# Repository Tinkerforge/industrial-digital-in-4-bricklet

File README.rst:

Industrial Digital In 4 Bricklet
================================

This repository contains the firmware source code and the hardware design
files. The documentation generator configs can be found at
https://github.com/Tinkerforge/generators

Repository Content
------------------

software/:
 * examples/: Examples for all supported languages
 * build/: Compiled files
 * src/: Source code of firmware
 * Makefile: Makefile to build project

hardware/:
 * Contains KiCad project files and additionally schematics as PDF

datasheets/:
 * Contains datasheets for sensors and complex ICs that are used

Hardware
--------

The hardware is designed with the open source EDA Suite KiCad
(http://www.kicad.org). Before you are able to open the files,
you have to install the Tinkerforge kicad-libraries
(https://github.com/Tinkerforge/kicad-libraries). You can either clone
them directly in hardware/ or clone them in a separate folder and
symlink them into hardware/
(ln -s kicad_path/kicad-libraries project_path/hardware). After that you
can open the .pro file in hardware/ with KiCad and from there view and
modify the schematics and the PCB layout.

Software
--------

If you want to do your own Brick/Bricklet firmware development we highly
recommend that you use our build environment setup script and read the
tutorial (https://www.tinkerforge.com/en/doc/Tutorials/Tutorial_Build_Environment/Tutorial.html).

To compile the C code we recommend you to install the newest GNU Arm Embedded
Toolchain (https://launchpad.net/gcc-arm-embedded/+download).
You also need to install bricklib (https://github.com/Tinkerforge/bricklib)
and brickletlib (https://github.com/Tinkerforge/brickletlib).

You can either clone it directly in software/src/ or clone it in a
separate folder and symlink it into software/src/
(ln -s bricklib_path/bricklib project_path/software/src/ and
ln -s brickletlib_path/brickletlib project_path/software/src/).
Finally make sure to have CMake installed
(http://www.cmake.org/cmake/resources/software.html).

After that you can build the firmware by invoking make in software/.
The firmware (.bin) can then be found in software/build/ and uploaded
with brickv (click button "Flashing" on start screen).

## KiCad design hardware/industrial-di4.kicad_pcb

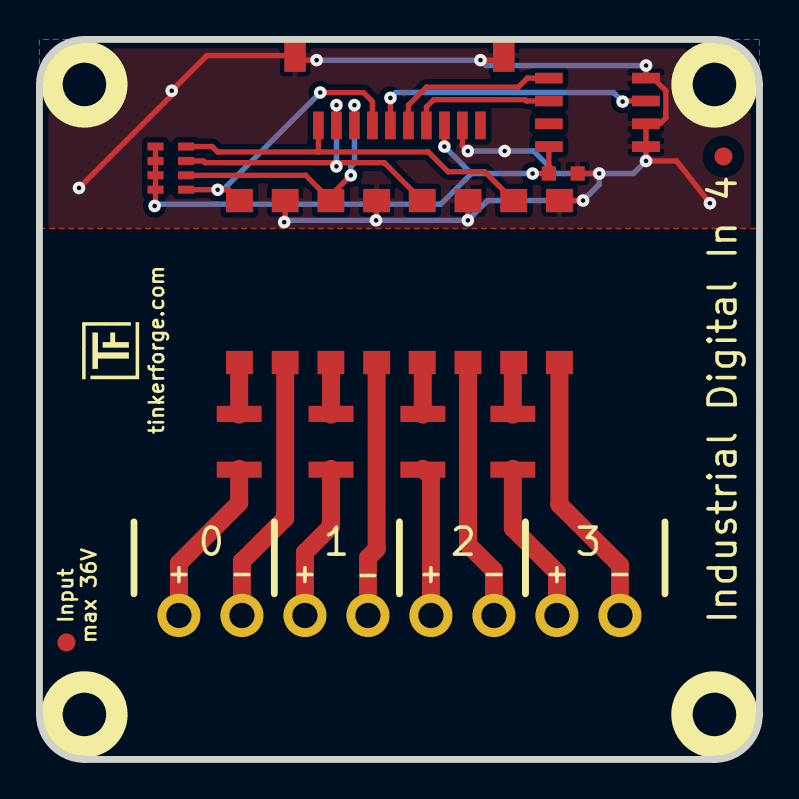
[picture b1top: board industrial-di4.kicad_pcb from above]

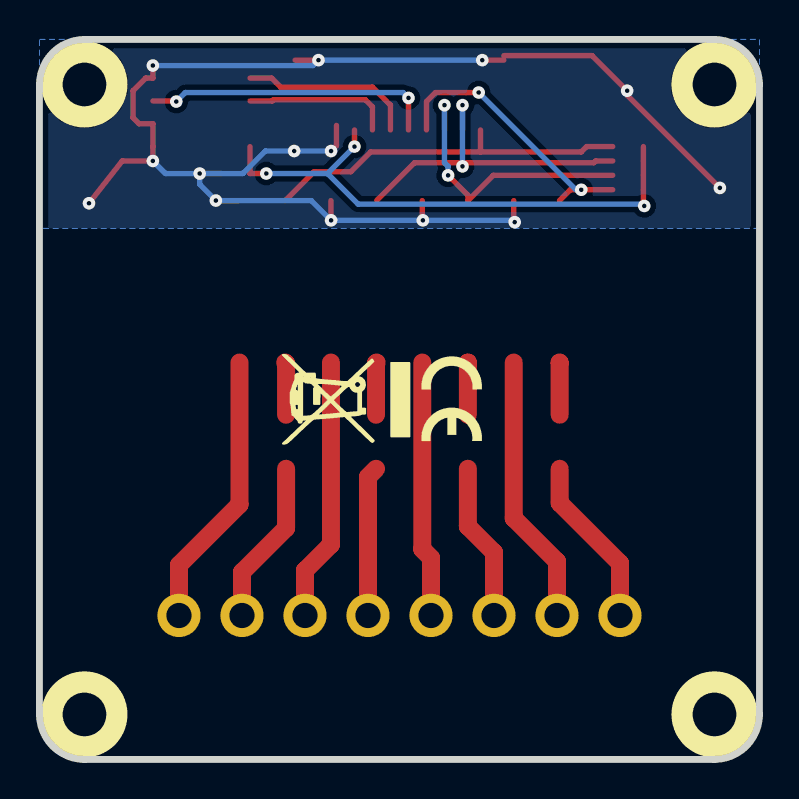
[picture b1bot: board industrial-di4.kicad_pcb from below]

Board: 2 copper layers, 40.0 x 40.0 mm, 18 parts (2 on the bottom side), 21 nets.

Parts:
C1: 100nF; C0603
Fiducial_Mark: VAL**; Fiducial_Mark
Fiducial_Mark#2: VAL**; Fiducial_Mark
P1: CON-SENSOR
P2: Digital Input; OQ_8P
R1, R2, R3, R4: 4.7k; R1210
RP1: 10k; 0603X4
U1: M24C64; SOIC8
U2: LTV846S; OPTO-SMD16
U3, U4, U5, U6: DRILL; DRILL_NP
VAL: WEEE_7mm
VAL#2: CE_5mm

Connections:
3V3: C1.1, P1.3, RP1.5, RP1.6, RP1.7, RP1.8, U1.8
GND: C1.2, P1.2, P1.EP, U1.1, U1.2, U1.4, U2.9, U2.11, U2.13, U2.15
INPUT1: P1.7, RP1.1, U2.16
INPUT2: P1.8, RP1.2, U2.14
INPUT3: P1.9, RP1.3, U2.12
INPUT4: P1.10, RP1.4, U2.10
unnamed: P1.4, U1.6
unnamed: P1.5, U1.5
unnamed: P1.6, U1.3
unnamed: P2.1, R1.2
unnamed: P2.2, U2.2
unnamed: P2.3, R2.2
unnamed: P2.4, U2.4
unnamed: P2.5, R3.2
unnamed: P2.6, U2.6
unnamed: P2.7, R4.2
unnamed: P2.8, U2.8
unnamed: R1.1, U2.1
unnamed: R2.1, U2.3
unnamed: R3.1, U2.5
unnamed: R4.1, U2.7

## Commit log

2012-10-24 Make cmake find the correct objcopy binary
    On some systems cmake uses the wrong objcopy binary, tell it to use
    the correct one.
2012-11-06 Add di4 source
2012-11-13 Support for protocol 2.0
2012-11-23 Add examples for c, csharp, delphi, java, php, python, ruby
2012-11-28 Industrial Digital In 4 hardware files added
2012-11-28 Fix parameter order in com_return_error calls
    Fix error handling in set_group.
2012-11-29 Make examples compatible to Protocol V2.0
2012-11-29 Make Ruby examples Protocol 2.0 compatible
2012-11-29 Make C examples Protocol 2.0 compatible
2012-11-29 Make Java examples Protocol 2.0 compatible
2012-11-29 Make PHP examples Protocol 2.0 compatible
2012-11-29 Make Delphi/Pascal examples Protocol 2.0 compatible
2012-11-30 delphi: Remove unnecessary parentheses and call destructor again
2012-12-05 Add protocol 2.0 compatability to C# bindings
2012-12-06 Fix C example
2012-12-11 Avoid g++ warnings about missing casts in C examples
2012-12-21 Fix wrong array size in destructor
2013-01-09 Use specific device object for callbacks
2013-01-17 Make Java examples compatible to new listener approach
2013-02-07 Use IPconnection disconnect explicitly in examples
2013-02-13 Add missing ReadKey call to C# example
2013-02-18 Add Visual Basic .NET examples
2013-07-17 Break long lines
2013-08-12 Add shell examples
2013-08-21 windows: Don't trigger a build in generate_makefile.bat
    Also use normal make instead of a special named one.
2013-08-28 Add edge counters for all pins
2014-01-08 delphi: Remove empty parentheses
2014-01-10 Add Perl examples
2014-01-14 perl: Fix subroutine signature
2014-01-15 php: Use const for constant values
2014-02-07 Add Mathematica examples
2014-02-07 delphi: Break long lines
2014-02-10 perl: fixed namespace
2014-02-11 javascript: adding examples
2014-02-11 javascript: short examples
2014-02-18 javascript: examples fixed
2014-02-20 javascript: add html examples
2014-02-24 javascript: port 4280, startExample()
2014-02-28 javascript: Break long lines and cleanup whitespace
2014-03-05 Add LabVIEW examples
2014-03-06 labview: Add examples in LV2010 format
2014-03-27 matlab: add examples
2014-04-02 java: Unify constants style
2014-04-02 perl: Unify print style
2014-04-17 matlab: Adapt examples to new callback style
2014-04-17 matlab: Add parentheses to make pygments happy
2014-07-15 java: Replace System.console() usage with an Eclipse compatible pattern
2014-12-02 Use ReadLine instead of ReadKey for C# example
2015-02-13 vbnet: Use ReadLine instead of ReadKey
    Because ReadKey doesn't work with a pipe as stdin on the RED Brick.
2015-03-02 windows: Stop cmake from searching for mingw32-make.exe
    Using MinGW Makefiles as generator makes cmake search for mingw32-make.exe
    which might not be installed because GnuWin32's make.exe is used instead.
2015-03-26 update hardware files to the newest version
2015-04-09 c: Whitespace
2015-06-24 javascript: Clean up output creation
2015-07-23 Make JavaScript browser example textarea readonly
2015-07-27 Cleanup C/C++, C#, Java, Python and Ruby examples
2015-07-29 Reformat changelog
2015-08-07 Use full device class name in Python examples
2015-08-12 Fix minor warnings in C/C++ examples
2015-08-14 Cleanup Delphi examples
2015-08-18 Cleanup VB.NET examples
2015-08-19 Cleanup Perl examples
2015-09-09 Duplicate cmake call to fix bug during cmake creation
2015-09-30 Generator based example cleanup
2015-10-13 Fix interrupt callback for grouped pins 8 to 15
2015-11-12 matlab: Fix callback handling for R2014a
    http://undocumentedmatlab.com/blog/matlab-callbacks-for-java-events-in-r2014a
2015-11-25 Include date and commit into changelog
2015-11-30 vbnet: Shorten long line
2016-05-18 c: Add missing device destroy call
2016-06-29 Whitespace
2016-07-01 Make the change UID comment more explicit
2017-04-13 csharp: Adapt example
2017-06-02 octave: Use javaObject instead of deprecated java_new
2017-07-28 New symbol for U2
2017-07-28 Add 3d information (final)
2017-07-28 Add 3d model (*.step & *.FCStd)
2017-07-31 Rename *.FCStd file
2017-11-30 Update examples from generator
2017-12-07 mathematica: Also generate .nb files
2018-01-26 c: Fine-tune printf format
2018-02-19 javascript: Close div tag correctly
2018-02-20 Cleanup KiCad libraries config
    Ensure LibDir=kicad-libraries and LibName1=tinkerforge.
    Remove special library.
2018-05-11 Rename files
2018-05-24 perl: Use strict in examples
2018-07-11 Add Makefile with docker support
2018-07-11 Remove obsolete generate_makefile scripts
2018-07-11 Update directory structure and build instructions
2018-11-06 Add rust examples
2018-11-07 rust: Accept host names for ip connection, fix naming inconsistencies
2018-11-07 rust: Rename callback receivers.
2018-12-14 Add go examples.
2018-12-18 go: Change import path.
2018-12-18 go: Change import path again.
2018-12-20 rust: Reformat examples.
2019-01-24 mqtt: Add examples.
2019-01-24 mqtt: Fix example header.
2019-01-24 mqtt: Remove executable bit in example permissions.
2019-01-24 go: Minor example fixes.
2019-01-24 mqtt: Minor example fixes.
2019-03-28 mqtt: Fix whitespace.
2019-08-22 c: Adapt to bindings changes
2020-01-13 examples: Use python3 input instead of python2 raw_input.
2020-01-13 examples: mqtt: Remove trailing whitespace.
2020-04-07 examples: rust: Always block when calling bindings functions.
2021-10-25 Update KiCad link
    https://www.kicad.org/blog/2021/10/Avoid-links-to-former-kicad-domain/
2022-07-06 Add license files.

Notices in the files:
hardware/industrial-di4.kicad_pcb:
Copyright Tinkerforge GmbH 2012.
This documentation describes Open Hardware and is licensed under the
CERN OHL v. 1.1.
